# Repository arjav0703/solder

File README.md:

This is a simple PCB that glows up depending on light (using a photoresistor)
---
### Images

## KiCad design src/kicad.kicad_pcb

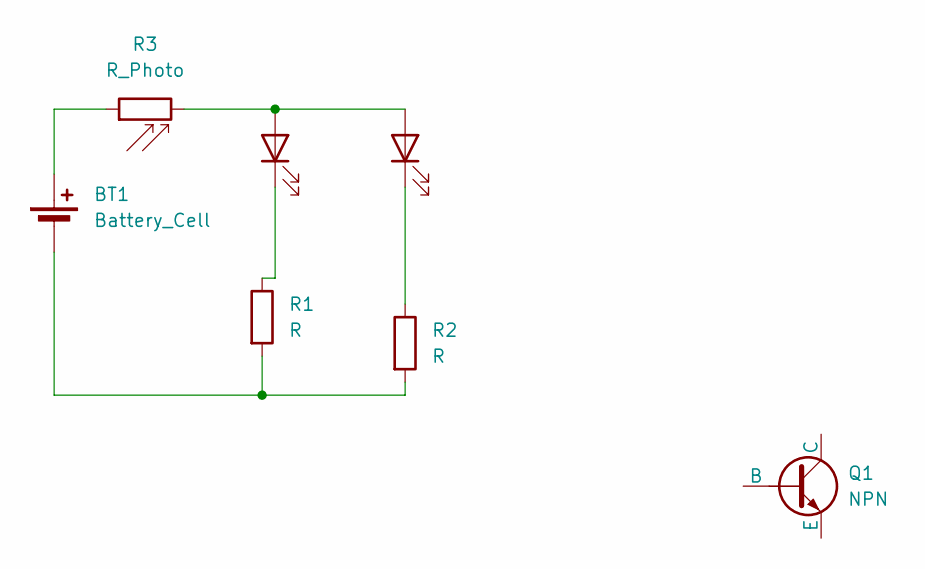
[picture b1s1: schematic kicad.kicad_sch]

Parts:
BT1: Battery_Cell; BatteryHolder_Keystone_3034_1x20mm
D1, D2: LED; LED_D5.0mm
Q1: NPN; TO-92L_HandSolder
R1, R2: R; R_Axial_DIN0207_L6.3mm_D2.5mm_P7.62mm_Horizontal
R3: R_Photo; R_LDR_5.0x4.1mm_P3mm_Vertical

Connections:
unnamed: BT1.1 (+), R3.1
unnamed: BT1.2 (-), R1.2, R2.2
unnamed: D1.2 (A), D2.2 (A), R3.2
unnamed: D1.1 (K), R1.1
unnamed: D2.1 (K), R2.1

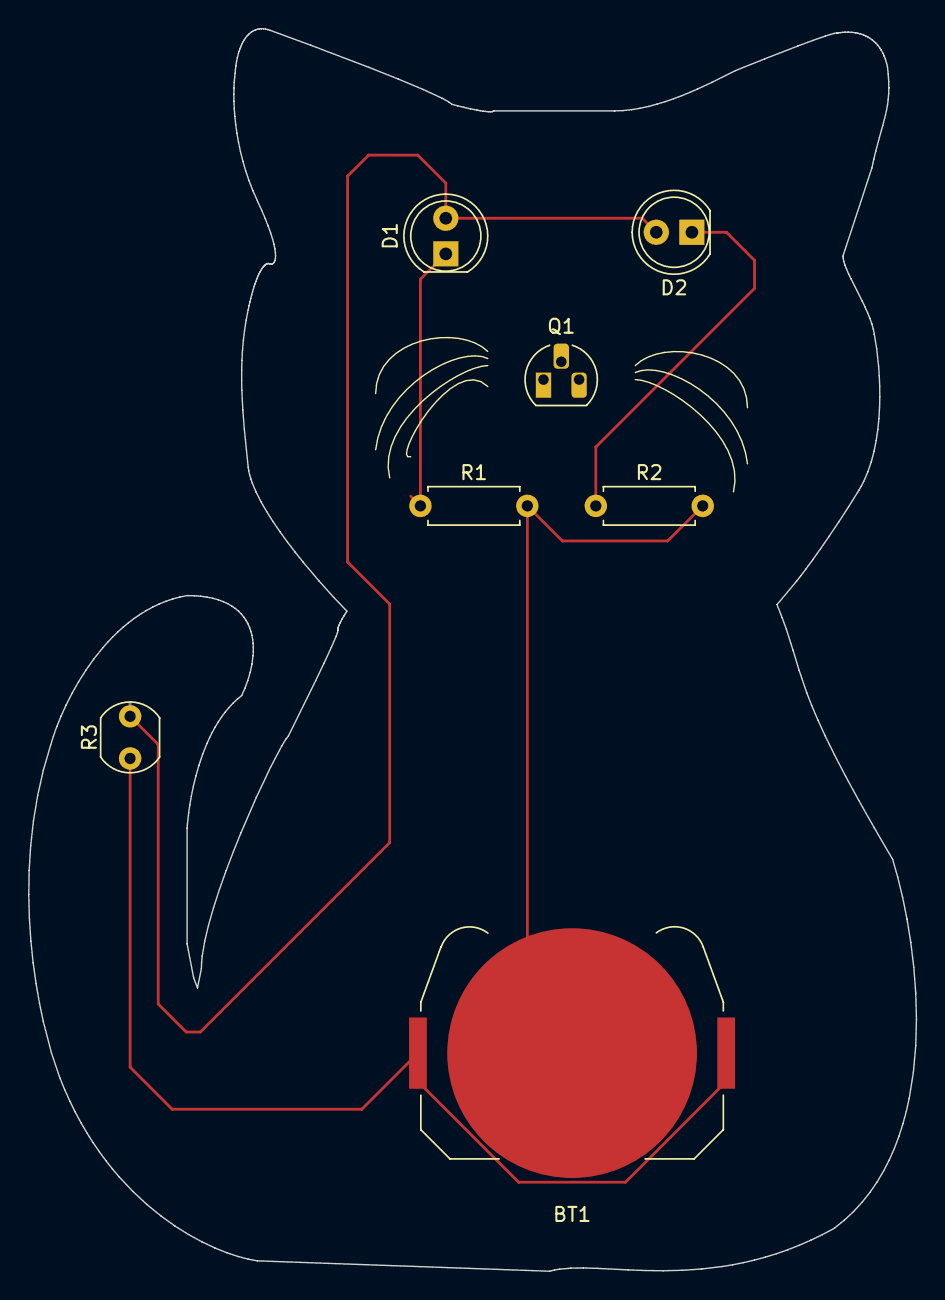
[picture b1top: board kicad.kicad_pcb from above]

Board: 2 copper layers, 63.3 x 88.6 mm, 7 parts (0 on the bottom side), 5 nets.

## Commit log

2025-04-23 hellow world
2025-04-23 organize
2025-04-23 update PCB
2025-04-23 add images
2025-04-23 add gerber
2025-04-23 update silkscreen
